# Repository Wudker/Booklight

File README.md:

# BookLight

BookLight is a compact clip-on LED lamp designed for reading in low-light conditions. Its lightweight, print-in-place structure can be attached directly to a book cover or pages, providing local illumination without a larger desk lamp. The project combines a simple LED circuit with a custom 3D-printed clip and spring mechanism.

## Technologies

`LED lighting` `CAD` `3D printing` `Print-in-place design` `Mechanical prototyping`

## Usage and development status

Attach the clip to the book cover or a small group of pages and position the LED above the reading area. The current version is a functional prototype. Future improvements include a redesigned printed spring, a more ergonomic clip mechanism and a refined enclosure.

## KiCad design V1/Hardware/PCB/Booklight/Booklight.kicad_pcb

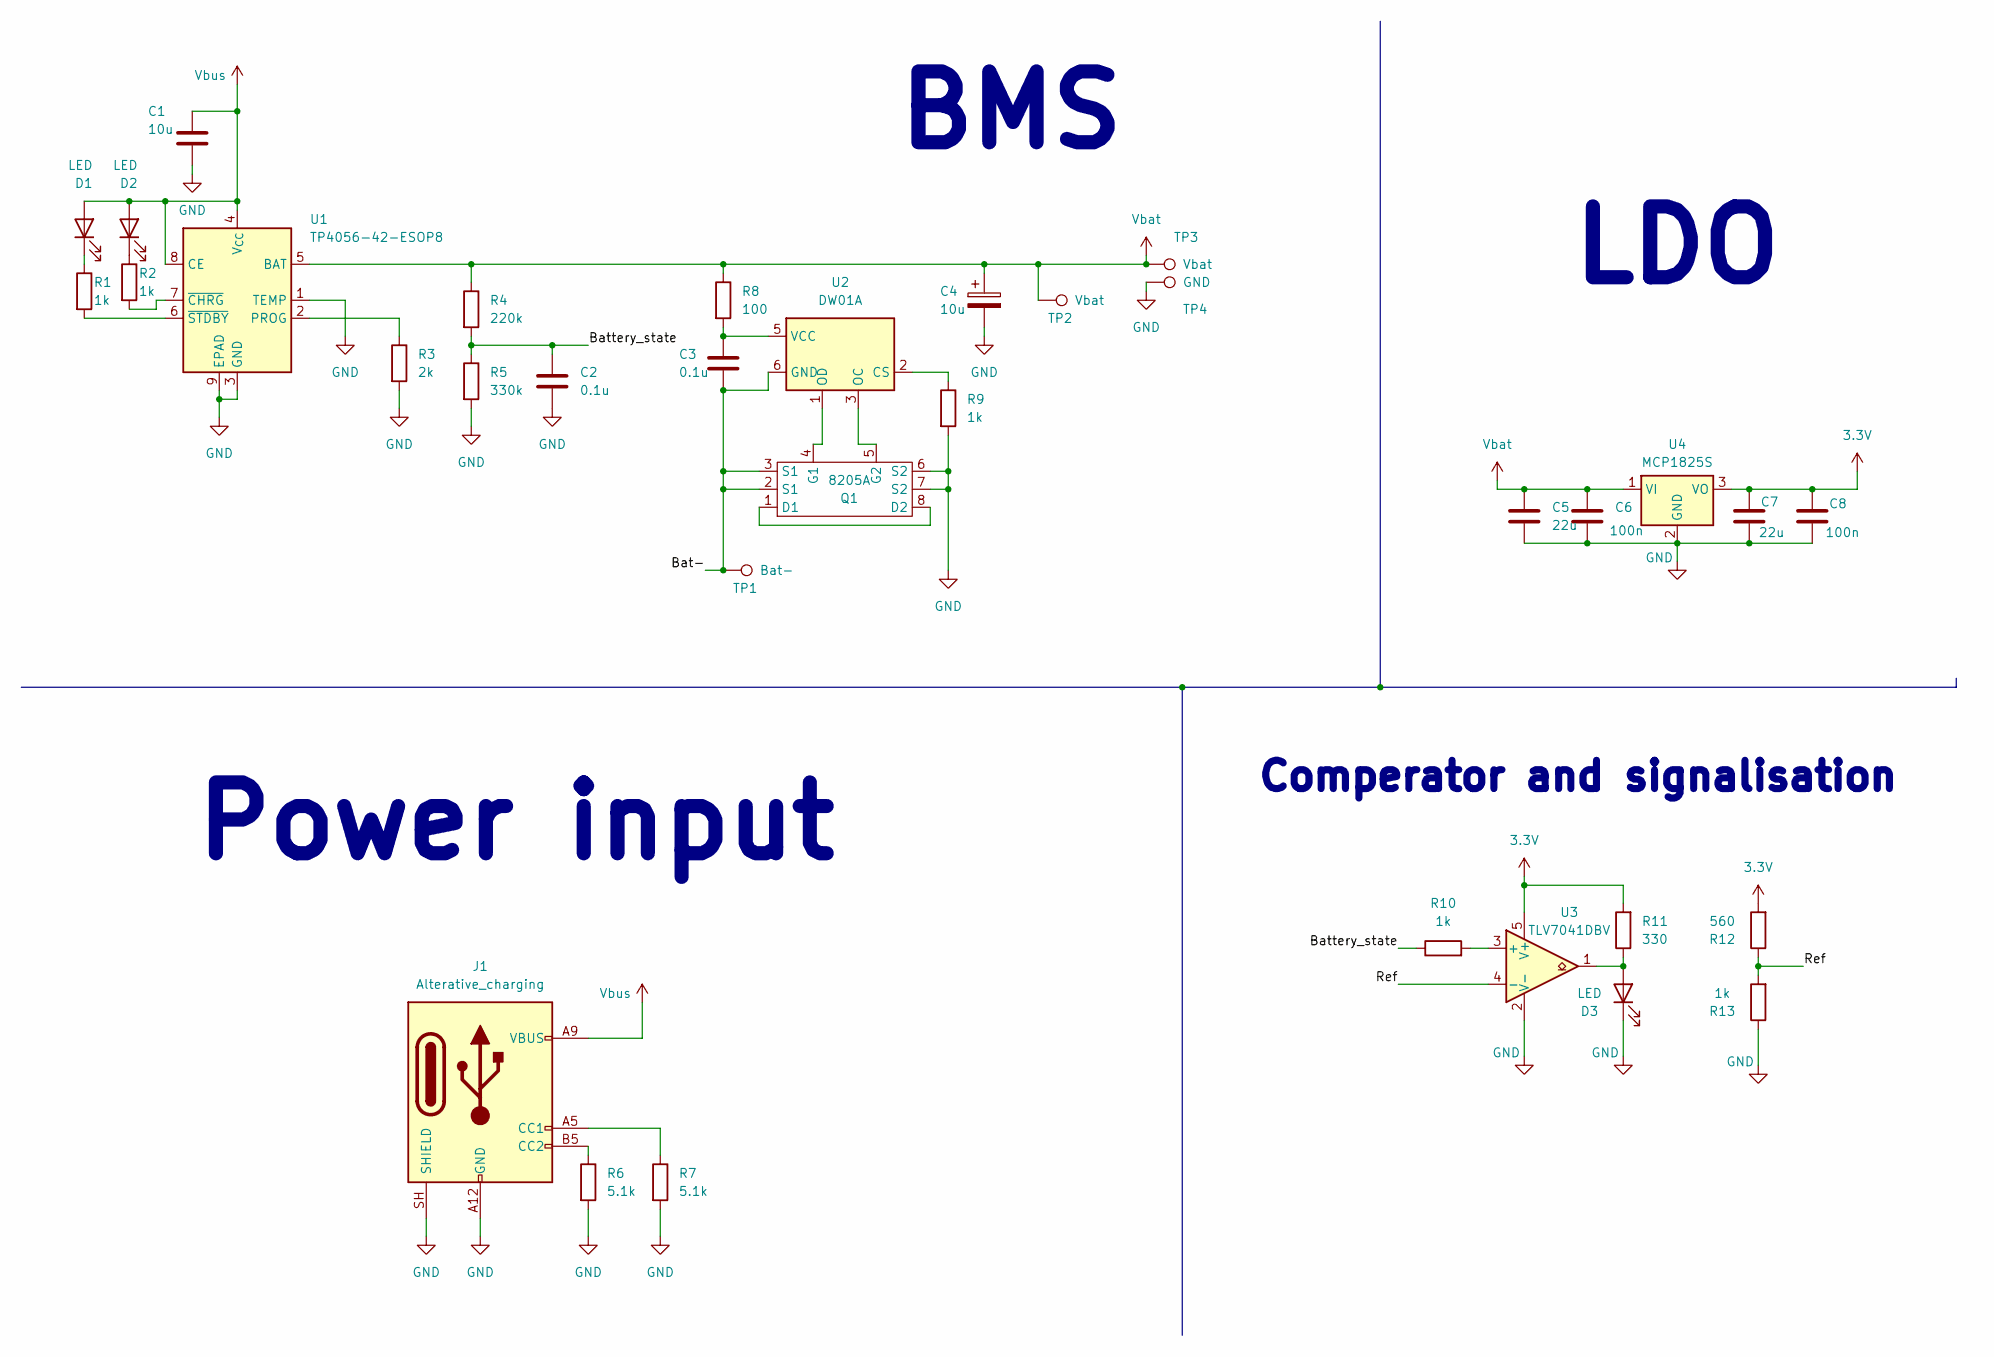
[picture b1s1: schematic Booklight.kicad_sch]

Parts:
C1, C4: 10u; C_1206_3216Metric
C2, C3: 0.1u; C_1206_3216Metric
C5, C7: 22u; C_1206_3216Metric
C6, C8: 100n; C_1206_3216Metric
D1, D2, D3: LED; LED_1206_3216Metric_Pad1.42x1.75mm_HandSolder
J1: Alterative_charging; USB_C_Receptacle_GCT_USB4125-xx-x-0190_6P_TopMnt_Horizontal
Q1: 8205A; TSSOP-8_4.4x3mm_P0.65mm
R1, R2, R9, R10, R13: 1k; R_1206_3216Metric
R3: 2k; R_1206_3216Metric
R4: 220k; R_1206_3216Metric
R5: 330k; R_1206_3216Metric
R6, R7: 5.1k; R_1206_3216Metric
R8: 100; R_1206_3216Metric
R11: 330; R_1206_3216Metric
R12: 560; R_1206_3216Metric
TP1: Bat-; TestPoint_Pad_D2.0mm
TP2, TP3: Vbat; TestPoint_Pad_D2.0mm
TP4: GND; TestPoint_Pad_D2.0mm
U1: TP4056-42-ESOP8; SOIC-8-1EP_3.9x4.9mm_P1.27mm_EP2.41x3.3mm_ThermalVias
U2: DW01A; SOT-23-6
U3: TLV7041DBV; SOT-23-5
U4: MCP1825S; SOT-223-3_TabPin2

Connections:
3.3V: C7.1, C8.1, R11.2, R12.2, U3.5 (V+), U4.3 (VO)
/Bat-: C3.1, Q1.2 (S1), Q1.3 (S1), TP1.1 (1_1), U2.6 (GND)
/Battery_state: C2.1, R4.2, R5.1, R10.1
/Ref: R12.1, R13.2, U3.4 (-)
GND: C1.2, C2.2, C4.2, C5.2, C6.2, C7.2, C8.2, D3.1 (K), J1.A12 (GND), J1.B12 (GND), J1.SH (SHIELD), Q1.6 (S2), Q1.7 (S2), R3.2, R5.2, R6.2, R7.2, R9.2, R13.1, TP4.1 (1_1), U1.1 (TEMP), U1.3 (GND), U1.9 (EPAD), U3.2 (V-), U4.2 (GND)
unnamed: D1.1 (K), R1.1
unnamed: D2.1 (K), R2.1
unnamed: D3.2 (A), R11.1, U3.1
unnamed: J1.A5 (CC1), R7.1
unnamed: J1.B5 (CC2), R6.1
unnamed: Q1.1 (D1), Q1.8 (D2)
unnamed: Q1.4 (G1), U2.1 (OD)
unnamed: Q1.5 (G2), U2.3 (OC)
unnamed: R3.1, U1.2 (PROG)
unnamed: R2.2, U1.7 (~CHRG)
unnamed: R1.2, U1.6 (~STDBY)
unnamed: R9.1, U2.2 (CS)
unnamed: C3.2, R8.2, U2.5 (VCC)
unnamed: R10.2, U3.3 (+)
Vbat: C4.1, C5.1, C6.1, R4.1, R8.1, TP2.1 (1_1), TP3.1 (1_1), U1.5 (BAT), U4.1 (VI)
Vbus: C1.1, D1.2 (A), D2.2 (A), J1.A9 (VBUS), J1.B9 (VBUS), U1.4 (V_{CC}), U1.8 (CE)

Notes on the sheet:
LDO
BMS
Power input
Comperator and signalisation

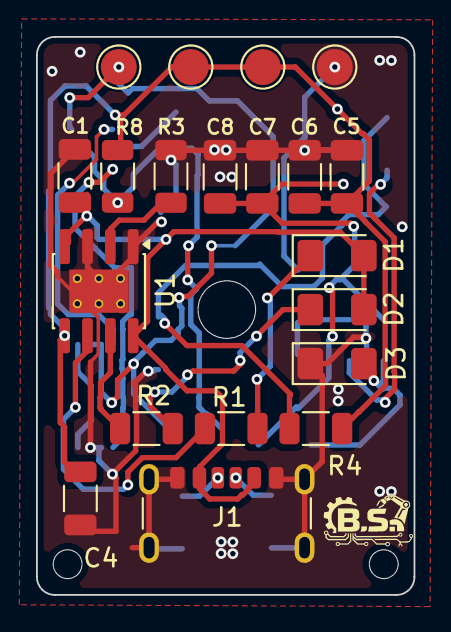
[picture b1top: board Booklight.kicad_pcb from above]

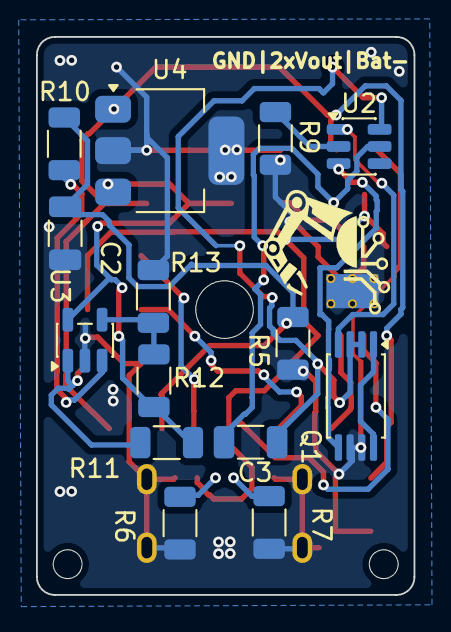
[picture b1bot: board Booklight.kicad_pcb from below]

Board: 2 copper layers, 21.0 x 31.0 mm, 34 parts (14 on the bottom side), 21 nets.

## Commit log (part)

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2026-06-27 Initial
2026-06-27 Update prototype hardware parts and assembly
    Add new STL parts (Battery_box, TP_box, lamp_head, lamp_starter, main_clip) and archive an older assembly version (OldVersions/main.0015.iam). Update lamp_link.stl and Prototype/Hardware/main.iam to 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
